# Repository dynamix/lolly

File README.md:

# lolly
Who does not like a LOLLY!

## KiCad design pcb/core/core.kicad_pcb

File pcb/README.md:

# lolly
Who does not like a LOLLY!

⠀⠀⠀⠀⠀⠀⠀⠀⠀⠀⠀⠀⠀⠀⠀⠀⠀⠀⠀⠀⠀⠀⠀⠀⠀⠀⠀⠀⠀⠀
⠀⠀⠀⠀⠀⠀⠀⠀⠀⠀⠀⠀⠀⠀⣀⣤⡶⠾⠿⠿⠷⠶⣦⣄⡀⠀⠀⠀⠀⠀
⠀⠀⠀⠀⠀⠀⠀⠀⠀⠀⠀⠀⣠⡾⠋⣁⣤⣶⣾⣿⣶⣦⣄⠙⠻⣦⡀⠀⠀⠀
⠀⠀⠀⠀⠀⠀⠀⠀⠀⠀⠀⣼⠟⢀⣾⣿⠟⠋⣉⣉⡉⠛⢿⣿⣄⠙⣷⡀⠀⠀
⠀⠀⠀⠀⠀⠀⠀⠀⠀⠀⢰⡟⢀⣿⡿⠁⣴⣿⠿⠿⣿⣶⡀⠻⣿⣇⢸⣇⠀⠀
⠀⠀⠀⠀⠀⠀⠀⠀⠀⠀⢸⡇⢸⣿⡇⢸⣿⡇⠀⣦⠈⢿⣿⠀⢻⣿⠀⣿⠀⠀
⠀⠀⠀⠀⠀⠀⠀⠀⠀⠀⠘⣧⠈⣿⣷⡀⠻⣿⣿⡿⢀⣾⣿⠀⣼⣿⠀⡏⠀⠀
⠀⠀⠀⠀⠀⠀⠀⠀⠀⠀⠀⢻⣆⠘⢿⣿⣦⣤⣠⣤⣾⡿⠋⣰⣿⡟⠘⠀⠀⠀
⠀⠀⠀⠀⠀⠀⠀⠀⠀⠀⢀⣄⠙⢷⣄⡉⠛⠿⠿⠛⠋⣠⣴⣿⠟⠀⠀⠀⠀⠀
⠀⠀⠀⠀⠀⠀⠀⠀⢀⣴⣿⠟⠀⠀⠉⠛⠓⠶⠶⠶⠿⠟⠛⠁⠀⠀⠀⠀⠀⠀
⠀⠀⠀⠀⠀⠀⢀⣴⣿⠟⠁⠀⠀⠀⠀⠀⠀⠀⠀⠀⠀⠀⠀⠀⠀⠀⠀⠀⠀⠀
⠀⠀⠀⠀⠀⣠⣿⠟⠁⠀⠀⠀⠀⠀⠀⠀⠀⠀⠀⠀⠀⠀⠀⠀⠀⠀⠀⠀⠀⠀
⠀⠀⠀⣠⣾⡿⠋⠀⠀⠀⠀⠀⠀⠀⠀⠀⠀⠀⠀⠀⠀⠀⠀⠀⠀⠀⠀⠀⠀⠀
⠀⠀⣼⠿⠋⠀⠀⠀⠀⠀⠀⠀⠀⠀⠀⠀⠀⠀⠀⠀⠀⠀⠀⠀⠀⠀⠀⠀⠀⠀
⠀⠀⠀⠀⠀⠀⠀⠀⠀⠀⠀⠀⠀⠀⠀⠀⠀⠀⠀⠀⠀⠀⠀⠀⠀⠀⠀⠀⠀⠀

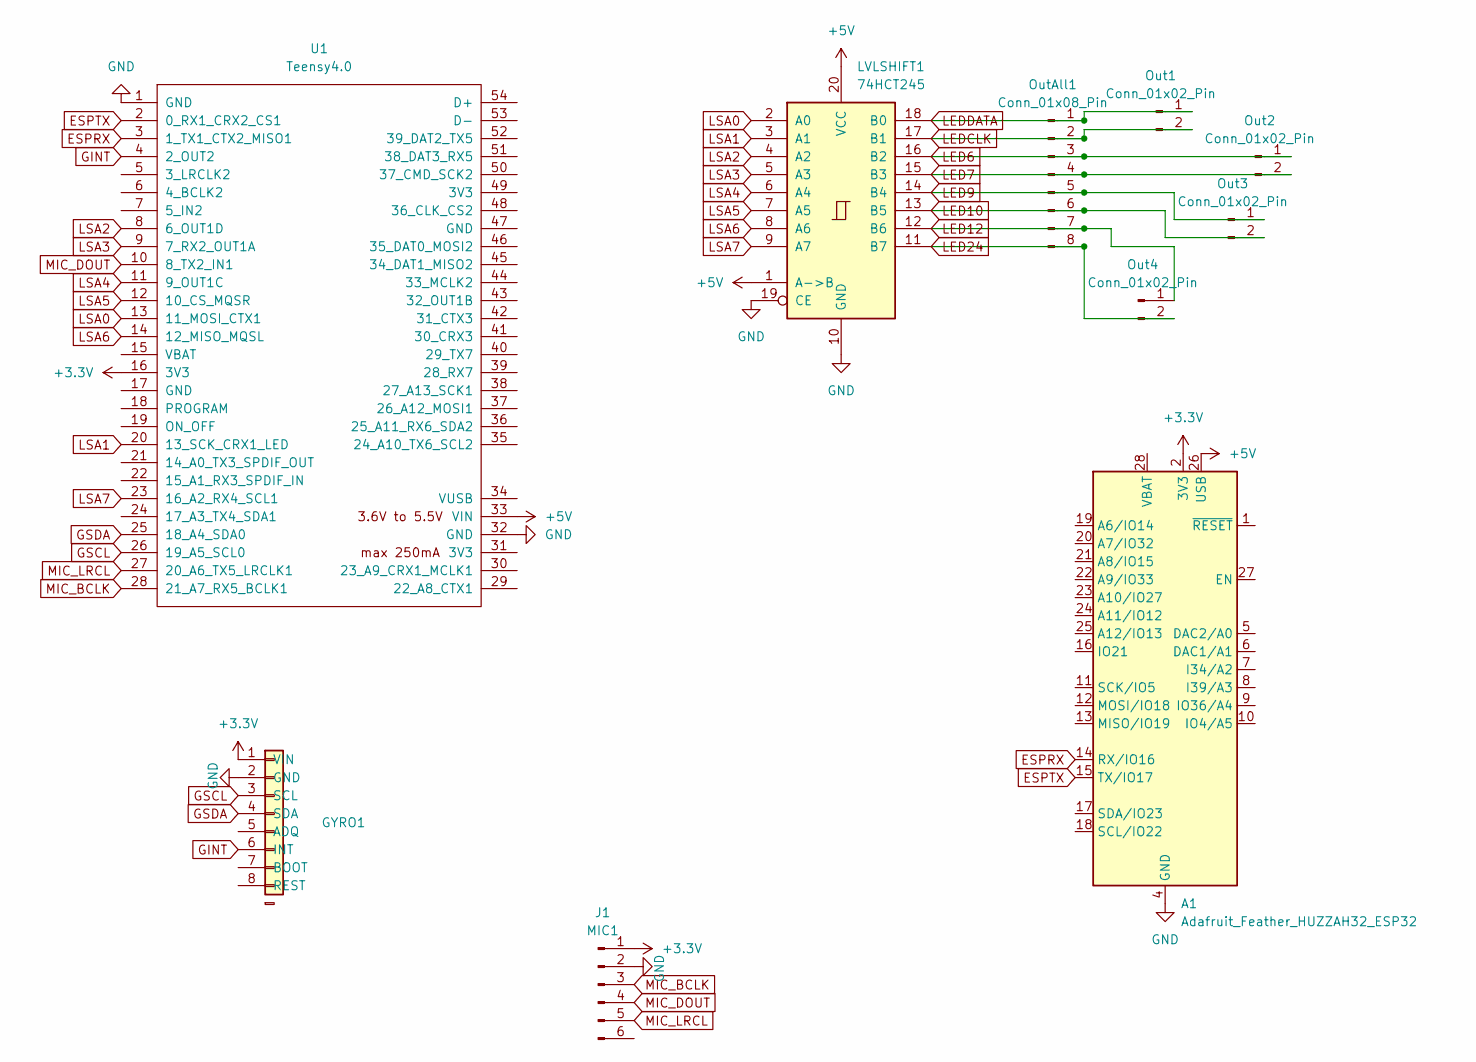
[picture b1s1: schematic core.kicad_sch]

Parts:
A1: Adafruit_Feather_HUZZAH32_ESP32; Adafruit_Feather
GYRO1: Conn_01x09; PinHeader_1x08_P2.54mm_Vertical
J1: MIC1; PinHeader_1x06_P2.54mm_Vertical
LVLSHIFT1: 74HCT245; SOIC-20W_7.5x12.8mm_P1.27mm
Out1, Out2, Out3, Out4: Conn_01x02_Pin; JST_PH_B2B-PH-K_1x02_P2.00mm_Vertical
OutAll1: Conn_01x08_Pin; PinHeader_1x08_P2.54mm_Vertical
U1: Teensy4.0; Teensy40

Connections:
+3.3V: A1.2 (3V3), GYRO1.1 (VIN), J1.1, U1.16 (3V3)
+5V: A1.26 (USB), LVLSHIFT1.1 (A->B), LVLSHIFT1.20 (VCC), U1.33 (VIN)
ESPRX: A1.14 (RX/IO16), U1.3 (1_TX1_CTX2_MISO1)
ESPTX: A1.15 (TX/IO17), U1.2 (0_RX1_CRX2_CS1)
GINT: GYRO1.6 (INT), U1.4 (2_OUT2)
GND: A1.4 (GND), GYRO1.2 (GND), J1.2, LVLSHIFT1.10 (GND), LVLSHIFT1.19 (CE), U1.1 (GND), U1.32 (GND)
GSCL: GYRO1.3 (SCL), U1.26 (19_A5_SCL0)
GSDA: GYRO1.4 (SDA), U1.25 (18_A4_SDA0)
LED6: LVLSHIFT1.16 (B2), Out2.1, OutAll1.3
LED7: LVLSHIFT1.15 (B3), Out2.2, OutAll1.4
LED9: LVLSHIFT1.14 (B4), Out3.1, OutAll1.5
LED10: LVLSHIFT1.13 (B5), Out3.2, OutAll1.6
LED12: LVLSHIFT1.12 (B6), Out4.1, OutAll1.7
LED24: LVLSHIFT1.11 (B7), Out4.2, OutAll1.8
LEDCLK: LVLSHIFT1.17 (B1), Out1.2, OutAll1.2
LEDDATA: LVLSHIFT1.18 (B0), Out1.1, OutAll1.1
LSA0: LVLSHIFT1.2 (A0), U1.13 (11_MOSI_CTX1)
LSA1: LVLSHIFT1.3 (A1), U1.20 (13_SCK_CRX1_LED)
LSA2: LVLSHIFT1.4 (A2), U1.8 (6_OUT1D)
LSA3: LVLSHIFT1.5 (A3), U1.9 (7_RX2_OUT1A)
LSA4: LVLSHIFT1.6 (A4), U1.11 (9_OUT1C)
LSA5: LVLSHIFT1.7 (A5), U1.12 (10_CS_MQSR)
LSA6: LVLSHIFT1.8 (A6), U1.14 (12_MISO_MQSL)
LSA7: LVLSHIFT1.9 (A7), U1.23 (16_A2_RX4_SCL1)
MIC_BCLK: J1.3, U1.28 (21_A7_RX5_BCLK1)
MIC_DOUT: J1.4, U1.10 (8_TX2_IN1)
MIC_LRCL: J1.5, U1.27 (20_A6_TX5_LRCLK1)

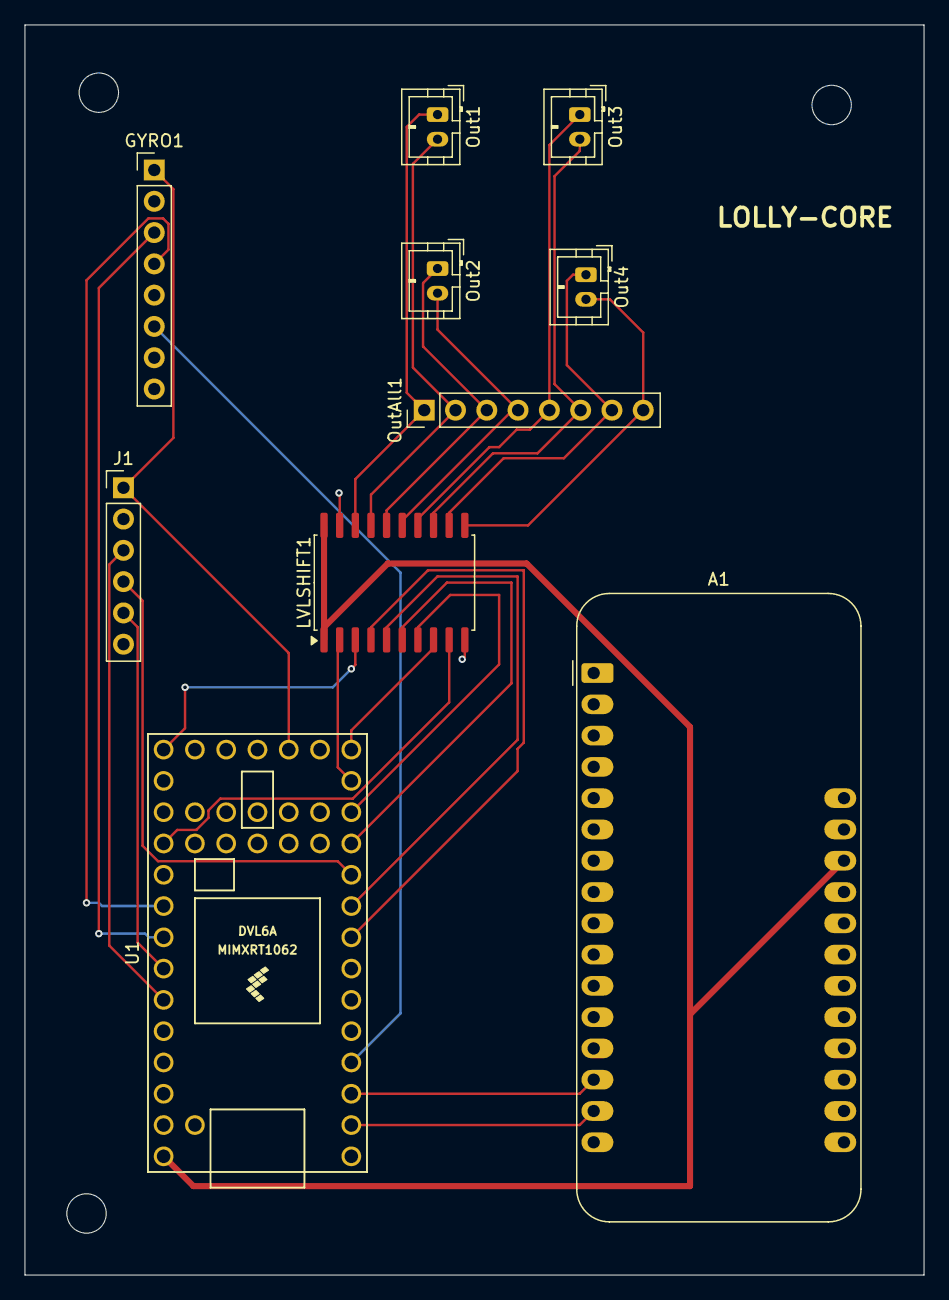
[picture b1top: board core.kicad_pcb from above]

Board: 2 copper layers, 73.0 x 101.5 mm, 10 parts (0 on the bottom side), 27 nets.

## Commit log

2024-06-13 get started
2024-06-13 lolly
2024-07-05 add v0 schema
2024-07-11 reorg and add firmware
2024-07-13 update mapping and tests
2024-07-18 latest changes
2024-07-18 celanup
2024-07-18 setup instructions and portable Makefile that works for people not called "Martin"
2024-07-18 I2C communication with input controller box, doesn't work yet
2024-07-19 add stuff
2024-08-12 add changes from festival
2025-07-09 add new main board
2025-07-09 update git ignore
2025-07-09 save
